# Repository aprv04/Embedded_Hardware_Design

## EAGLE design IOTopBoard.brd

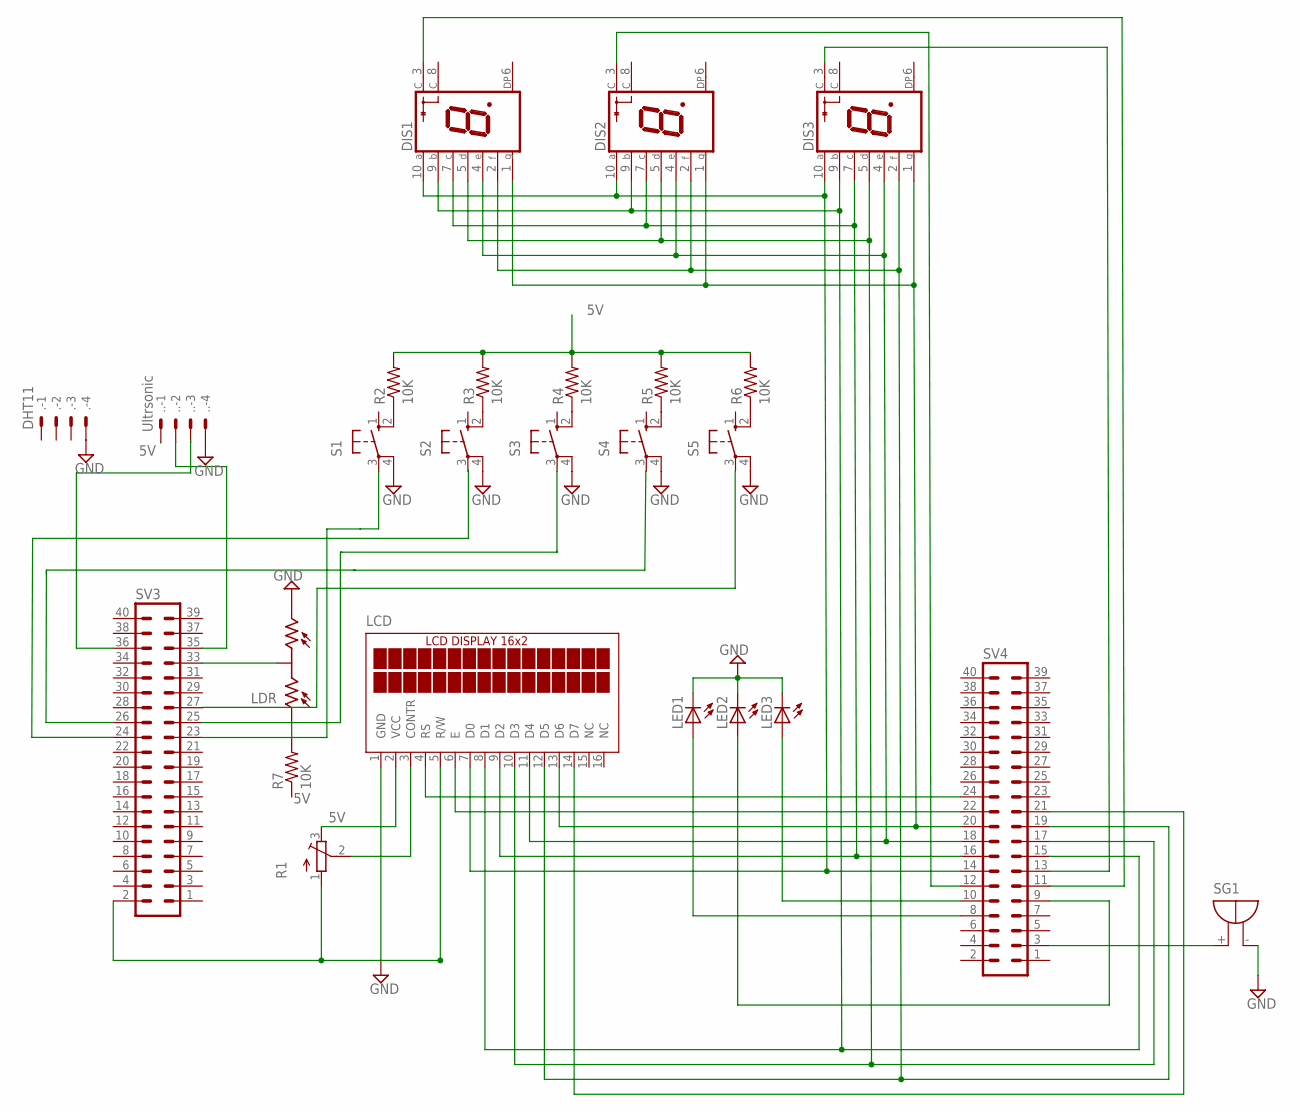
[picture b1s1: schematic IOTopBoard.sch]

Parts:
.: DHT11; 22-23-2041
..: Ultrsonic; 22-23-2041
DIS1, DIS2, DIS3: S4301B
LCD: TUXGR_16X2_R2
LDR: VT83CT; VT800CT
LED1, LED2, LED3: LED_E; LED_1206
R1: TRIM_EU-3223W; 3223W
R2, R3, R4, R5, R6, R7: 10K; R1206
S1, S2, S3, S4, S5: 10-XX; B3F-10XX
SG1: F/HMB
SV3, SV4: MA20-2

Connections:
5V: LCD.2 (VCC), LCD.3 (CONTR), R1.2 (S), R1.3 (E), R2.2, R3.2, R4.2, R5.2, R6.2, R7.1
GND: LCD.1 (GND), LCD.5 (R/W), LDR.3, LED1.C, LED2.C, LED3.C, R1.1 (A), S1.4 (P1), S2.4 (P1), S3.4 (P1), S4.4 (P1), S5.4 (P1), SG1.-, SV3.2
unnamed: LCD.6 (E), SV4.22
unnamed: DIS1.3 (C), SV4.11
unnamed: LCD.14 (D7), SV4.21
unnamed: DIS2.3 (C), SV4.12
unnamed: DIS3.3 (C), SV4.13
unnamed: SG1.+, SV4.3
unnamed: LDR.2, SV3.33
unnamed: R2.1, S1.2 (S1)
unnamed: R3.1, S2.2 (S1)
unnamed: LCD.4 (RS), SV4.24
unnamed: R4.1, S3.2 (S1)
unnamed: R5.1, S4.2 (S1)
unnamed: DIS1.10 (A), DIS2.10 (A), DIS3.10 (A), LCD.7 (D0), SV4.14
unnamed: LED3.A, SV4.10
unnamed: LED1.A, SV4.8
unnamed: LED2.A, SV4.9
unnamed: R6.1, S5.2 (S1)
unnamed: LDR.1, R7.2
unnamed: DIS1.7 (C), DIS2.7 (C), DIS3.7 (C), LCD.9 (D2), SV4.16
unnamed: DIS1.5 (D), DIS1.9 (B), DIS2.5 (D), DIS2.9 (B), DIS3.5 (D), DIS3.9 (B), LCD.8 (D1), LCD.10 (D3), SV4.15, SV4.17
unnamed: DIS1.4 (E), DIS2.4 (E), DIS3.4 (E), LCD.11 (D4), SV4.18
unnamed: DIS1.2 (F), DIS2.2 (F), DIS3.2 (F), LCD.12 (D5), SV4.19
unnamed: DIS1.1 (G), DIS2.1 (G), DIS3.1 (G), LCD.13 (D6), SV4.20

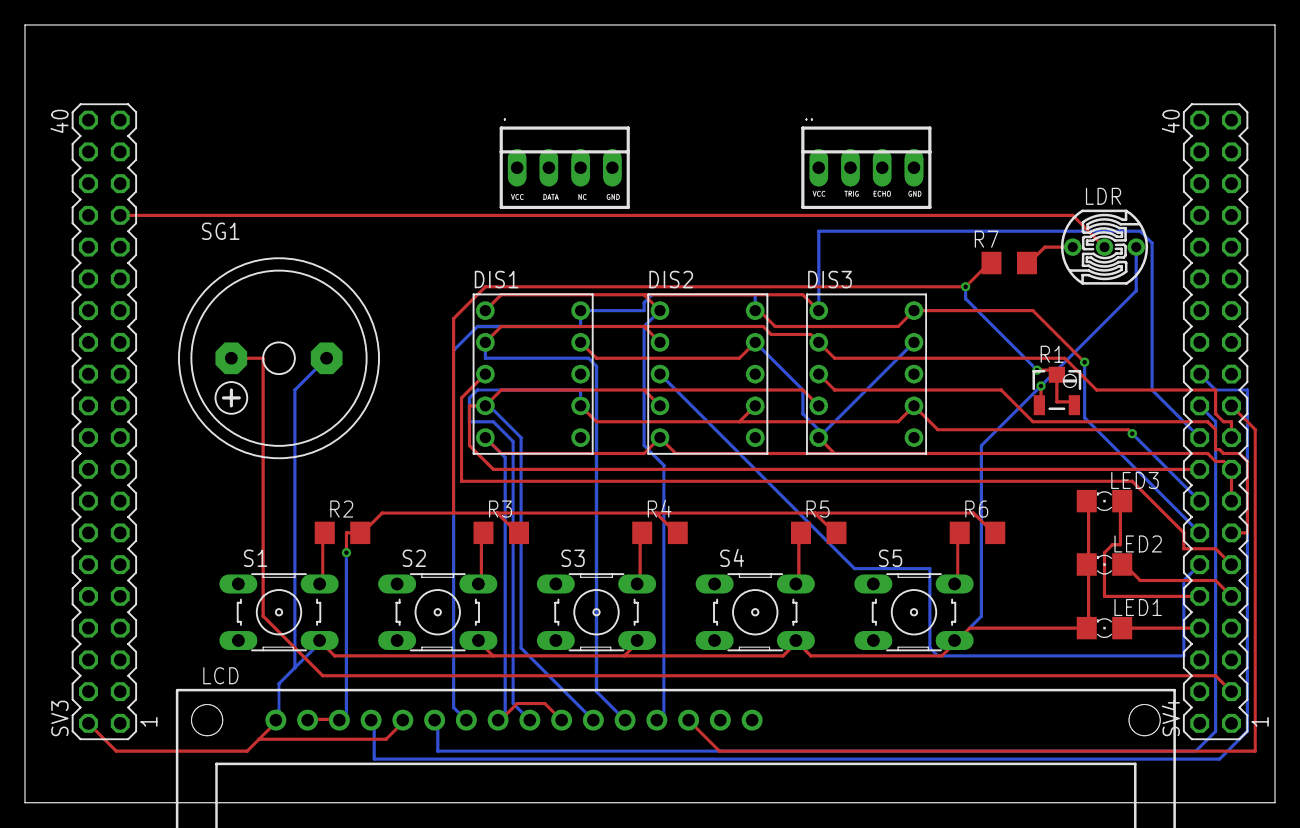
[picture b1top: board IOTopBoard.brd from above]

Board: 2 copper layers, 100.0 x 62.2 mm, 25 parts (0 on the bottom side), 25 nets.

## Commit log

2019-01-28 Multibot
